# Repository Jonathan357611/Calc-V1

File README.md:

# Calc V1 🧮

This is RP2040 (Raspberry Pi Pico) driven calculator using mechanical switches based on the MX-format which doubles as an HID-numpad if wanted.

This is my very first *real* physical and polished project and thus im very proud of it as a 15 year old :)

## PCB

The 2 sided PCB was designed in kicad and some rookie experience!
You can find the design files in the kicad folder and production in gerber.

## Installation 📀

Before installing, it is very important to flash **circuipy** on your Pico. You can download the newest version [here](https://circuitpython.org/board/raspberry_pi_pico/)

Now there are two options:

### Installer (only linux tested!):
1. Open a terminal
2. run ```git clone https://github.com/Jonathan357611/Calc-V1.git```
3. ... and now ```./installer.sh```. The installer should copy all necessary files to your Pico!
4. Done!

### Manual

1. Clone the repo ```git clone https://github.com/Jonathan357611/Calc-V1.git```
2. Take these files: code.py font5x8.bin lib/
3. And copy them on your Pico!

That should be it. If you have any troubles installing it, hit me up!

## HID Numpad
Want to use it as a numpad? Easy!
Just set ```HID``` to ```True``` in line 7 in code.py!

## Other

Any contributions in code, installation and PCB are very welcomed :)
I'll try my best to fix any issues you run into.

If you *really* like my project, consider donating some ETH :)
```0x1f2C6e62622051b3F4d4a3545B17018704630c35```

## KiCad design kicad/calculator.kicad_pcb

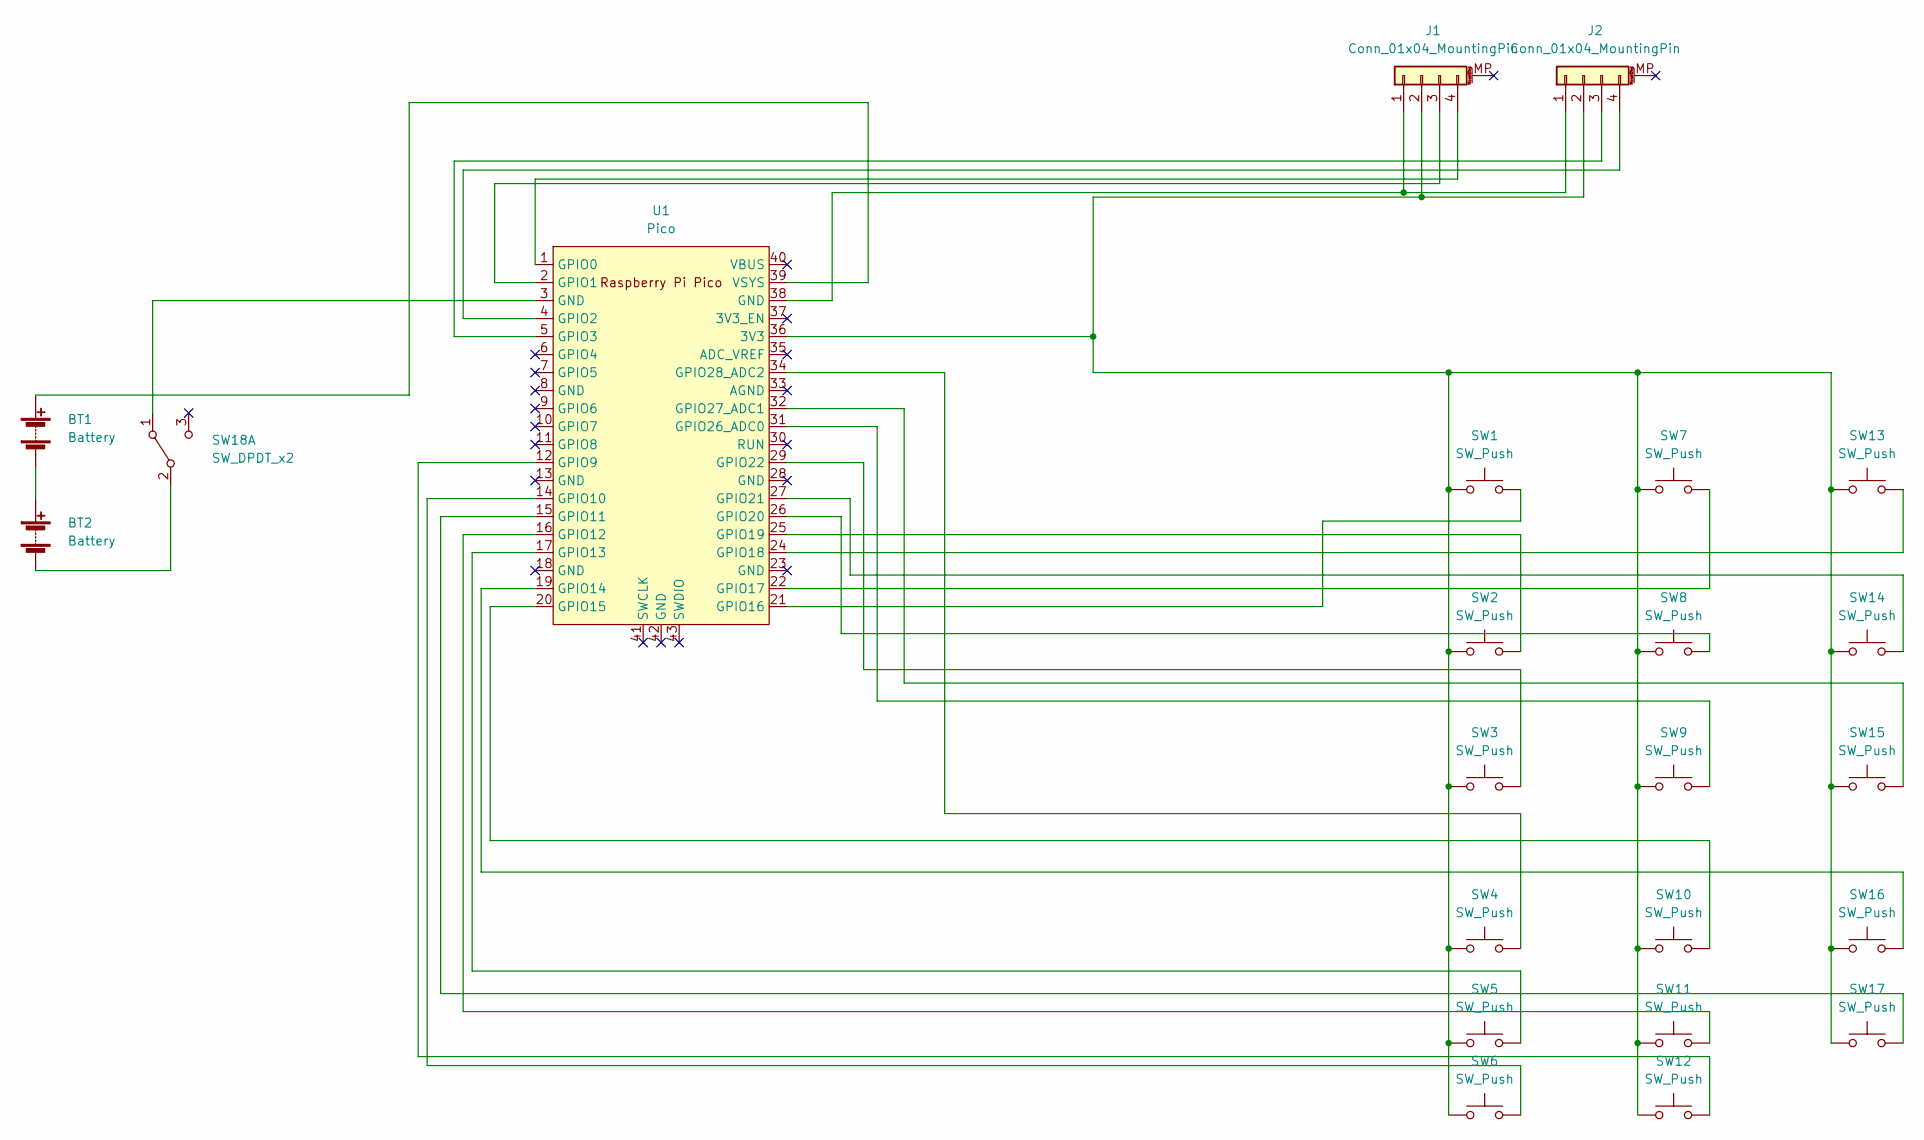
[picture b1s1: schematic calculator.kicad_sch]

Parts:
BT1, BT2: Battery; BatteryHolder_Keystone_2460_1xAA
J1, J2: Conn_01x04_MountingPin; 128x64OLED
SW1, SW2, SW3, SW4, SW5, SW6, SW7, SW11, SW12, SW13, SW14, SW15, SW16, SW17: SW_Push; SW_Cherry_MX_1.00u_PCB
SW8: SW_Push; SW_Cherry_MX_2.00u_PCB
SW9, SW10: SW_Push; SW_Cherry_MX_2.00u_Vertical_PCB
SW18: SW_DPDT_x2; PinSocket_1x03_P2.54mm_Vertical
U1: Pico; RPi_Pico_SMD_TH

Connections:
unnamed: BT1.1 (+), U1.39 (VSYS)
unnamed: BT1.2 (-), BT2.1 (+)
unnamed: BT2.2 (-), SW18.2 (B)
unnamed: J1.1, J2.1, U1.38 (GND)
unnamed: J1.2, J2.2, SW1.1, SW2.1, SW3.1, SW4.1, SW5.1, SW6.1, SW7.1, SW8.1, SW9.1, SW10.1, SW11.1, SW12.1, SW13.1, SW14.1, SW15.1, SW16.1, SW17.1, U1.36 (3V3)
unnamed: J1.3, U1.2 (GPIO1)
unnamed: J1.4, U1.1 (GPIO0)
unnamed: J2.3, U1.5 (GPIO3)
unnamed: J2.4, U1.4 (GPIO2)
unnamed: SW1.2, U1.21 (GPIO16)
unnamed: SW2.2, U1.25 (GPIO19)
unnamed: SW3.2, U1.29 (GPIO22)
unnamed: SW4.2, U1.34 (GPIO28_ADC2)
unnamed: SW5.2, U1.17 (GPIO13)
unnamed: SW6.2, U1.14 (GPIO10)
unnamed: SW7.2, U1.22 (GPIO17)
unnamed: SW8.2, U1.26 (GPIO20)
unnamed: SW9.2, U1.31 (GPIO26_ADC0)
unnamed: SW10.2, U1.20 (GPIO15)
unnamed: SW11.2, U1.16 (GPIO12)
unnamed: SW12.2, U1.12 (GPIO9)
unnamed: SW13.2, U1.24 (GPIO18)
unnamed: SW14.2, U1.27 (GPIO21)
unnamed: SW15.2, U1.32 (GPIO27_ADC1)
unnamed: SW16.2, U1.19 (GPIO14)
unnamed: SW17.2, U1.15 (GPIO11)
unnamed: SW18.1 (A), U1.3 (GND)

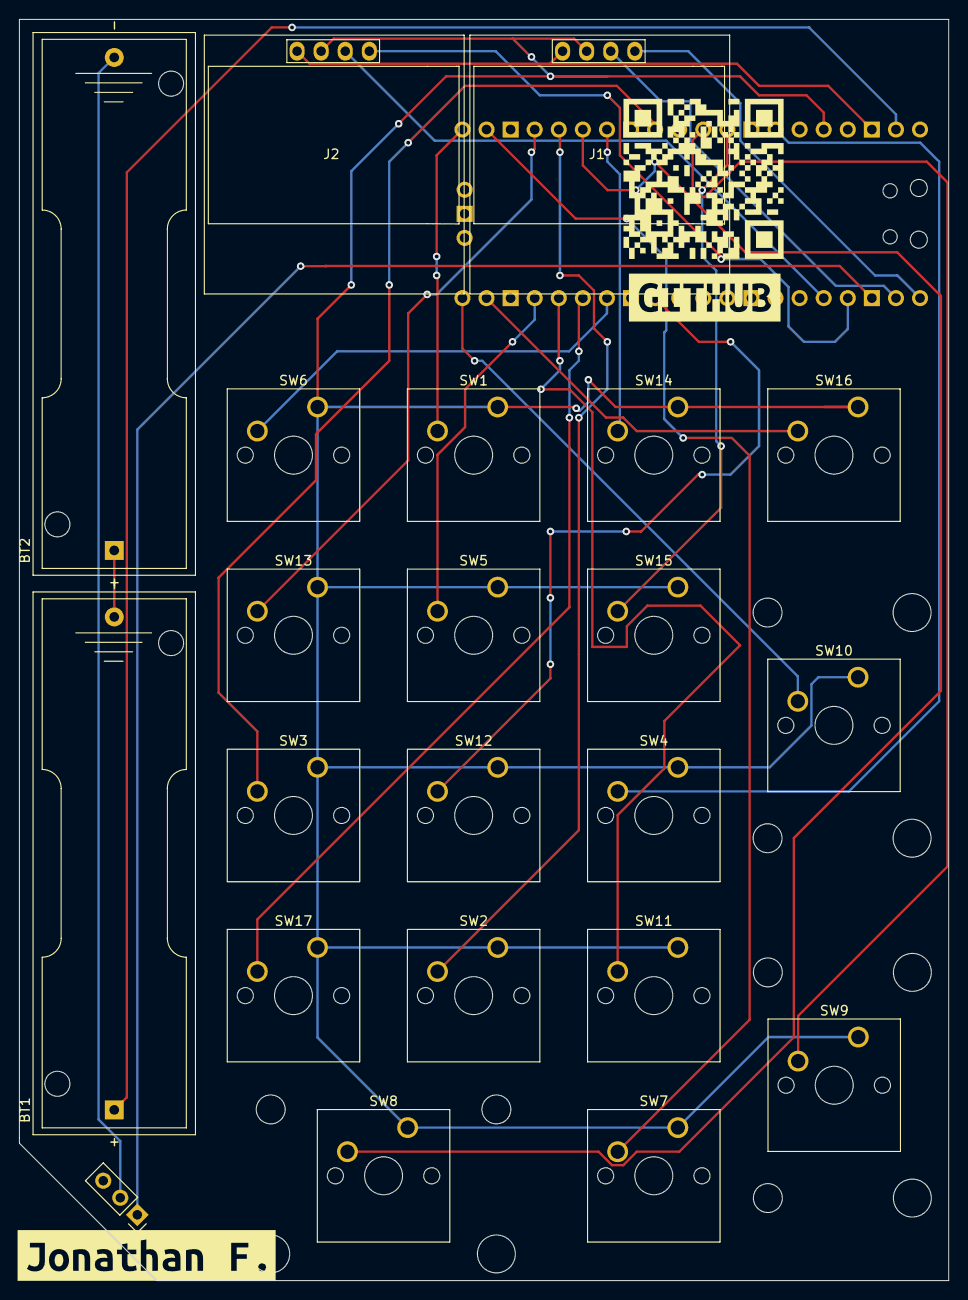
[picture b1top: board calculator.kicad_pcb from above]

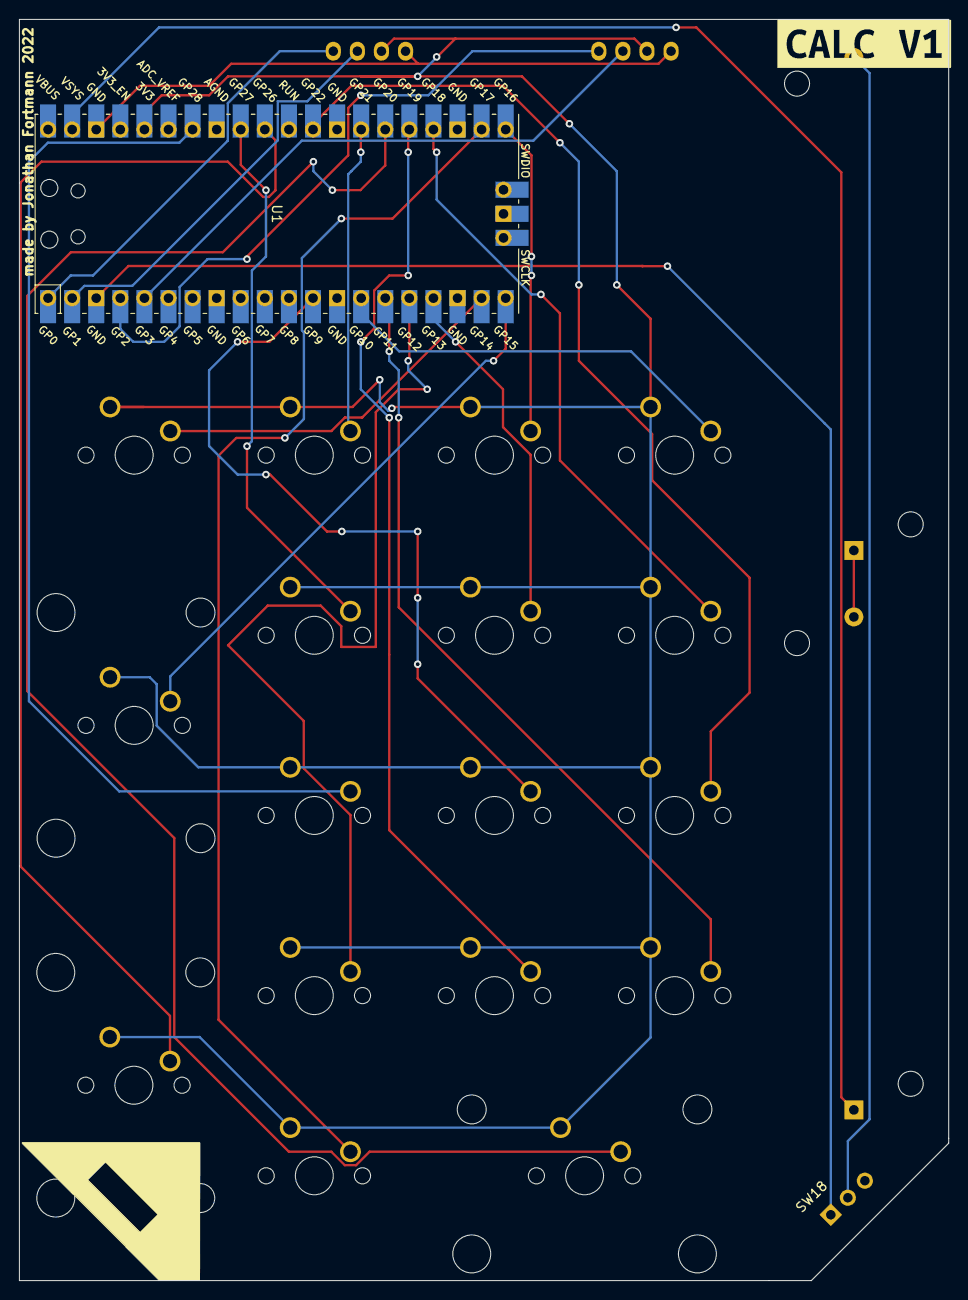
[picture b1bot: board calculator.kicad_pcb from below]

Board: 2 copper layers, 98.0 x 133.0 mm, 26 parts (2 on the bottom side), 27 nets.

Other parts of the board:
kibuzzard-630FA8E9: G***; kibuzzard-630FA8E9
kibuzzard-630FA917: G***; kibuzzard-630FA917
kibuzzard-63110344: G***; kibuzzard-63110344

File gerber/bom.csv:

Designator,Footprint,Quantity,Value,LCSC Part #
SW12,SW_Cherry_MX_1.00u_PCB,1,SW_Push,
SW7,SW_Cherry_MX_1.00u_PCB,1,SW_Push,
SW11,SW_Cherry_MX_1.00u_PCB,1,SW_Push,
SW15,SW_Cherry_MX_1.00u_PCB,1,SW_Push,
SW3,SW_Cherry_MX_1.00u_PCB,1,SW_Push,
SW13,SW_Cherry_MX_1.00u_PCB,1,SW_Push,
SW1,SW_Cherry_MX_1.00u_PCB,1,SW_Push,
SW10,SW_Cherry_MX_2.00u_Vertical_PCB,1,SW_Push,
SW2,SW_Cherry_MX_1.00u_PCB,1,SW_Push,
SW18,PinSocket_1x03_P2.54mm_Vertical,1,SW_DPDT_x2,
SW8,SW_Cherry_MX_2.00u_PCB,1,SW_Push,
BT1,BatteryHolder_Keystone_2460_1xAA,1,Battery,
SW6,SW_Cherry_MX_1.00u_PCB,1,SW_Push,
SW9,SW_Cherry_MX_2.00u_Vertical_PCB,1,SW_Push,
BT2,BatteryHolder_Keystone_2460_1xAA,1,Battery,
SW14,SW_Cherry_MX_1.00u_PCB,1,SW_Push,
J2,128x64OLED,1,Conn_01x04_MountingPin,
SW17,SW_Cherry_MX_1.00u_PCB,1,SW_Push,
SW5,SW_Cherry_MX_1.00u_PCB,1,SW_Push,
J1,128x64OLED,1,Conn_01x04_MountingPin,
SW16,SW_Cherry_MX_1.00u_PCB,1,SW_Push,
SW4,SW_Cherry_MX_1.00u_PCB,1,SW_Push,
U1,RPi_Pico_SMD_TH,1,Pico,

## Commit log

2022-09-20 initial
2022-09-20 README
2022-09-20 v1 commit
2022-09-20 updated status msgs
2022-09-20 spelling
2023-02-14 Updated my age
    Do I really have to do that every year??
